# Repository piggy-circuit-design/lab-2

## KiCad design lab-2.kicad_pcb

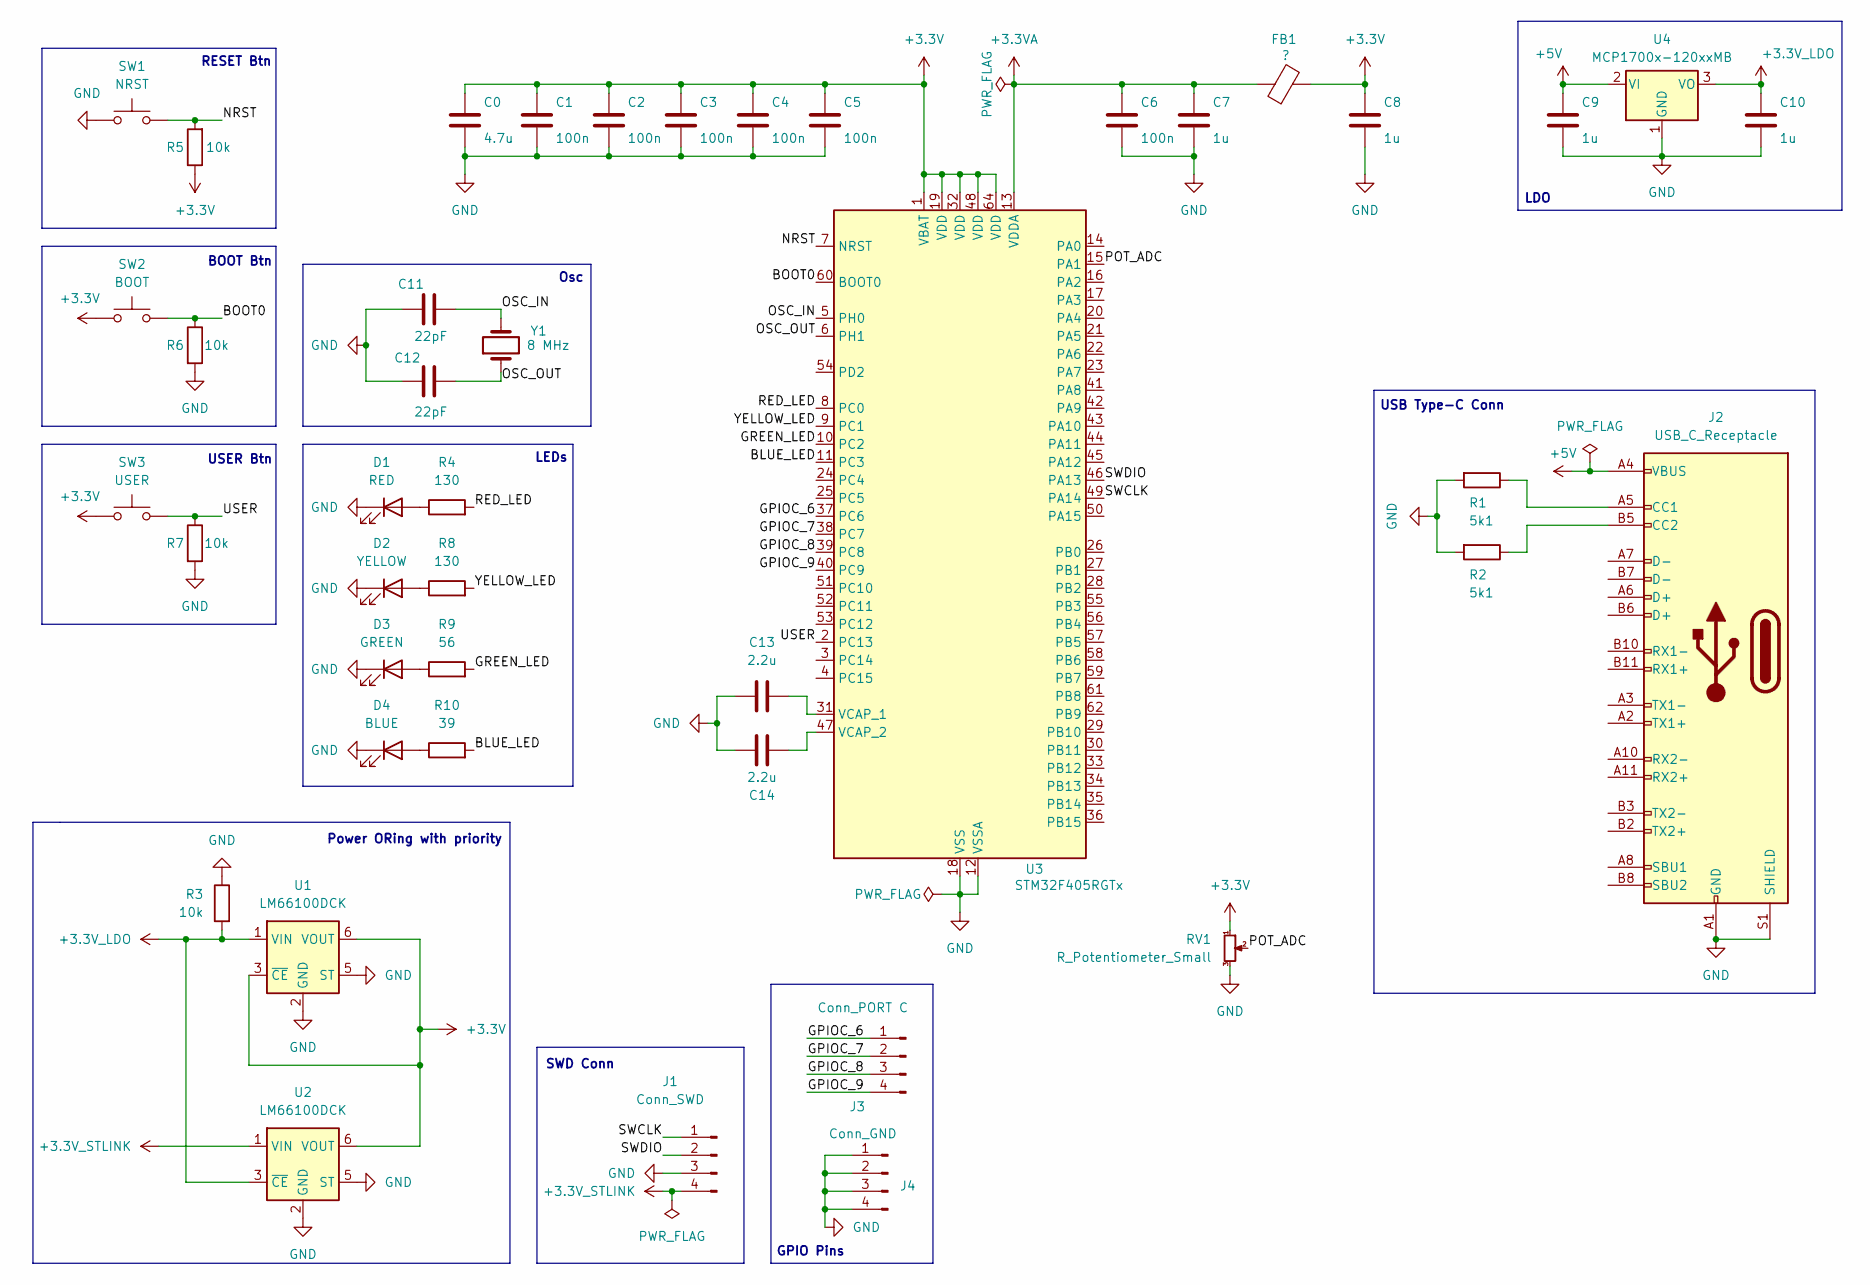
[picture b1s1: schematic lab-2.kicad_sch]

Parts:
C0: 4.7u; C_0603_1608Metric
C1, C2, C3, C4, C5, C6: 100n; C_0402_1005Metric
C7, C8, C9, C10: 1u; C_0603_1608Metric
C11, C12: 22pF; C_0402_1005Metric
C13, C14: 2.2u; C_0402_1005Metric
D1: RED; LED_0805_2012Metric
D2: YELLOW; LED_0805_2012Metric
D3: GREEN; LED_0805_2012Metric
D4: BLUE; LED_0805_2012Metric
FB1: ?; L_0603_1608Metric
J1: Conn_SWD; PinHeader_1x04_P2.54mm_Vertical
J2: USB_C_Receptacle; USB_C_Receptacle_Amphenol_12401610E4-2A
J3: Conn_PORT C; PinHeader_1x04_P2.54mm_Vertical
J4: Conn_GND; PinHeader_1x04_P2.54mm_Vertical
R1, R2: 5k1; R_0603_1608Metric
R3: 10k; R_0603_1608Metric
R4, R8: 130; R_0402_1005Metric
R5, R6, R7: 10k; R_0402_1005Metric
R9: 56; R_0402_1005Metric
R10: 39; R_0402_1005Metric
RV1: R_Potentiometer_Small; Potentiometer_Bourns_3224G_Horizontal
SW1: NRST; SW_SPST_PTS647_Sx38
SW2: BOOT; SW_SPST_PTS647_Sx38
SW3: USER; SW_SPST_PTS647_Sx38
U1, U2: LM66100DCK; SOT-363_SC-70-6
U3: STM32F405RGTx; LQFP-64_10x10mm_P0.5mm
U4: MCP1700x-120xxMB; SOT-89-3
Y1: 8 MHz; Crystal_SMD_2520-4Pin_2.5x2.0mm

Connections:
+3.3V: C0.1, C1.1, C2.1, C3.1, C4.1, C5.1, C8.1, FB1.2, R5.1, RV1.1, SW2.2, SW3.2, U1.3 (~CE), U1.6 (VOUT), U2.6 (VOUT), U3.1 (VBAT), U3.19 (VDD), U3.32 (VDD), U3.48 (VDD), U3.64 (VDD)
+3.3VA: C6.1, C7.1, FB1.1, U3.13 (VDDA)
+3.3V_LDO: C10.1, R3.2, U1.1 (VIN), U2.3 (~CE), U4.3 (VO)
+3.3V_STLINK: J1.4, U2.1 (VIN)
+5V: C9.1, J2.A4 (VBUS), J2.A9 (VBUS), J2.B4 (VBUS), J2.B9 (VBUS), U4.2 (VI)
/BLUE_LED: R10.2, U3.11 (PC3)
/BOOT0: R6.1, SW2.1, U3.60 (BOOT0)
/GPIOC_6: J3.1, U3.37 (PC6)
/GPIOC_7: J3.2, U3.38 (PC7)
/GPIOC_8: J3.3, U3.39 (PC8)
/GPIOC_9: J3.4, U3.40 (PC9)
/GREEN_LED: R9.2, U3.10 (PC2)
/NRST: R5.2, SW1.1, U3.7 (NRST)
/OSC_IN: C11.2, U3.5 (PH0), Y1.2
/OSC_OUT: C12.2, U3.6 (PH1), Y1.1
/POT_ADC: RV1.2, U3.15 (PA1)
/RED_LED: R4.2, U3.8 (PC0)
/SWCLK: J1.1, U3.49 (PA14)
/SWDIO: J1.2, U3.46 (PA13)
/USER: R7.1, SW3.1, U3.2 (PC13)
/YELLOW_LED: R8.2, U3.9 (PC1)
GND: C0.2, C1.2, C2.2, C3.2, C4.2, C5.2, C6.2, C7.2, C8.2, C9.2, C10.2, C11.1, C12.1, C13.1, C14.2, D1.1 (K), D2.1 (K), D3.1 (K), D4.1 (K), J1.3, J2.A1 (GND), J2.A12 (GND), J2.B1 (GND), J2.B12 (GND), J2.S1 (SHIELD), J2.SH, J4.1, J4.2, J4.3, J4.4, R1.2, R2.2, R3.1, R6.2, R7.2, RV1.3, SW1.2, U1.2 (GND), U1.5 (ST), U2.2 (GND), U2.5 (ST), U3.12 (VSSA), U3.18 (VSS), U3.63 (VSS), U4.1 (GND)
unnamed: D1.2 (A), R4.1
unnamed: D2.2 (A), R8.1
unnamed: D3.2 (A), R9.1
unnamed: D4.2 (A), R10.1
unnamed: J2.A5 (CC1), R1.1
unnamed: J2.B5 (CC2), R2.1
unnamed: C13.2, U3.31 (VCAP_1)
unnamed: C14.1, U3.47 (VCAP_2)

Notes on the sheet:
LEDs
BOOT Btn
SWD Conn
Osc
USB Type-C Conn
Power ORing with priority
LDO
GPIO Pins
RESET Btn
USER Btn

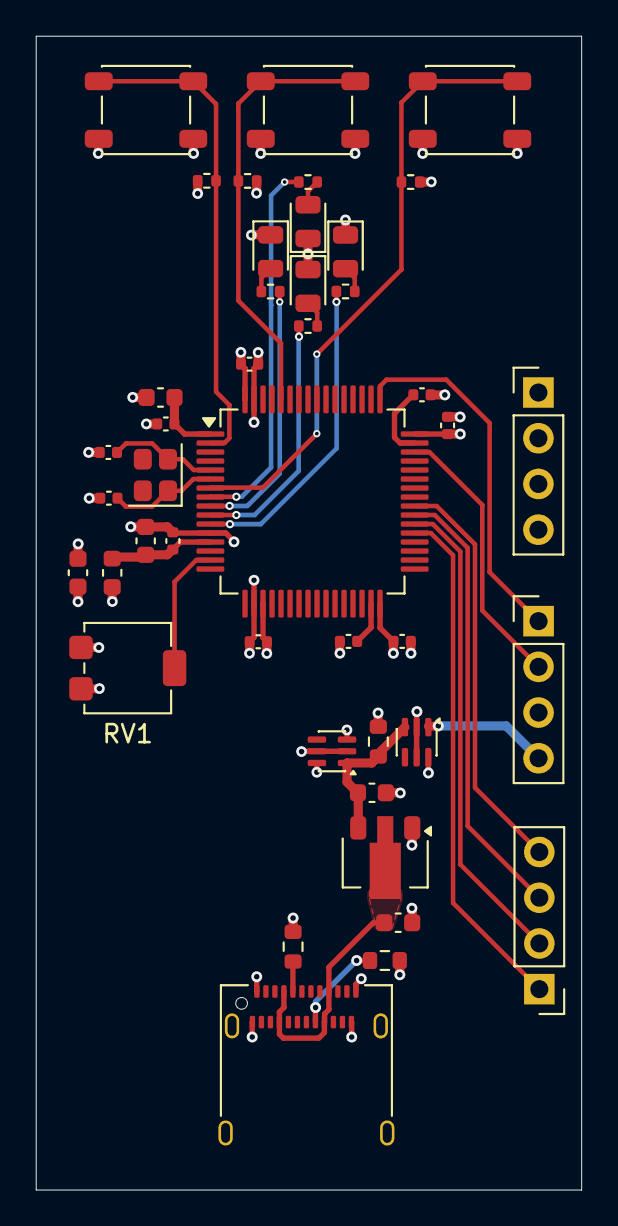
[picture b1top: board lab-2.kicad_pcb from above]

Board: 4 copper layers, 30.3 x 64.1 mm, 43 parts (0 on the bottom side), 30 nets.

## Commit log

2026-04-05 Init commit (took the lab-1 final result)
2026-04-05 Added 2 new layers + GPIO port A (4 pins)
2026-04-06 add USER button and LEDs
2026-04-09 added potentiometer
2026-04-12 fix some ERC and DRC issues
